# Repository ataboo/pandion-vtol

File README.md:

# Pandion VTOL

## Notes to Future

### Making Aft Prop Bi-directional

1. Connect to flight controller, test connection with BF-Configurator, but disconnect after.
2. Connect BL-Heli Configurator F-H-40 16.7, flash new or just configur as bi-directional.

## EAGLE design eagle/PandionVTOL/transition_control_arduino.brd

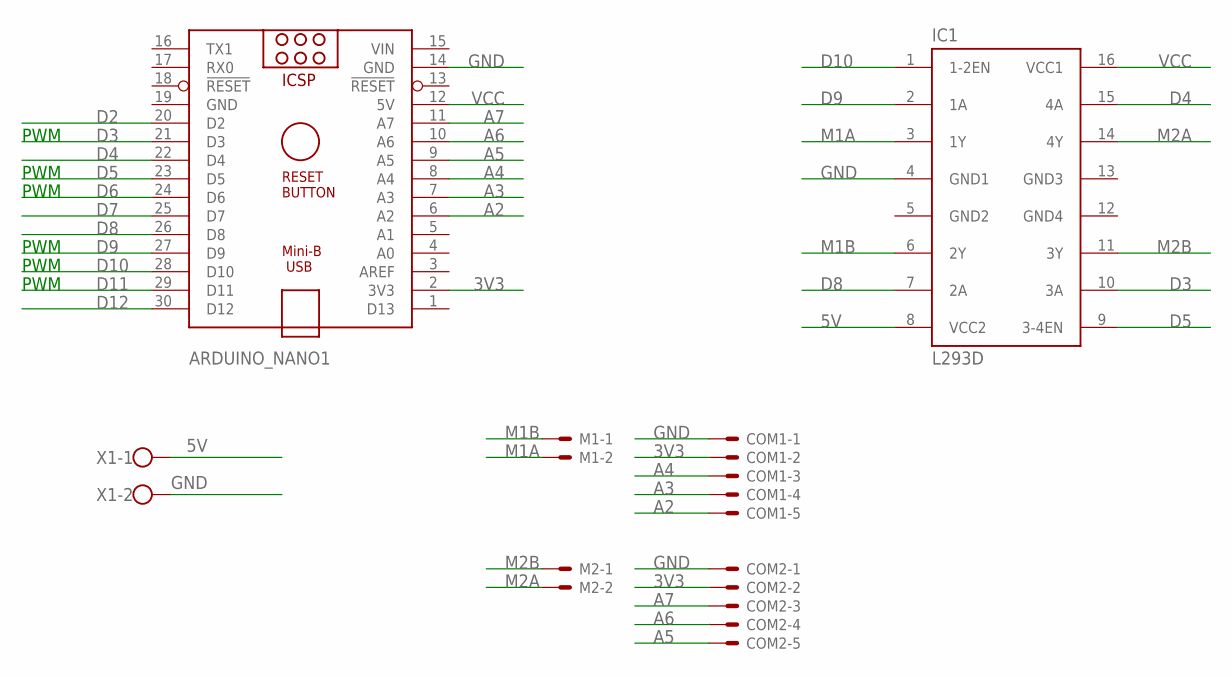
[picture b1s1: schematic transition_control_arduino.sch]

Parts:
ARDUINO_NANO1: ARDUINO_NANO
COM1, COM2: JST-XH-05-PIN-ROUND-PAD; JST-XH-05-PACKAGE-ROUND-PAD
IC1: L293D; DIL16
M1, M2: JST-XH-02-PIN-ROUND-PAD; JST-XH-02-PACKAGE-ROUND-PAD
X1: W237-102

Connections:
3V3: ARDUINO_NANO1.2 (3V3), COM1.2, COM2.2
5V: IC1.8 (VCC2), X1.1
A2: ARDUINO_NANO1.6 (A2), COM1.5
A3: ARDUINO_NANO1.7 (A3), COM1.4
A4: ARDUINO_NANO1.8 (A4), COM1.3
A5: ARDUINO_NANO1.9 (A5), COM2.5
A6: ARDUINO_NANO1.10 (A6), COM2.4
A7: ARDUINO_NANO1.11 (A7), COM2.3
D2: ARDUINO_NANO1.20 (D2)
D3: ARDUINO_NANO1.21 (D3), IC1.10 (3A)
D4: ARDUINO_NANO1.22 (D4), IC1.15 (4A)
D5: ARDUINO_NANO1.23 (D5), IC1.9 (3-4EN)
D6: ARDUINO_NANO1.24 (D6)
D7: ARDUINO_NANO1.25 (D7)
D8: ARDUINO_NANO1.26 (D8), IC1.7 (2A)
D9: ARDUINO_NANO1.27 (D9), IC1.2 (1A)
D10: ARDUINO_NANO1.28 (D10), IC1.1 (1-2EN)
D11: ARDUINO_NANO1.29 (D11)
D12: ARDUINO_NANO1.30 (D12)
GND: ARDUINO_NANO1.14 (GND), ARDUINO_NANO1.19 (GND), COM1.1, COM2.1, IC1.4 (GND1), X1.2
GND2: IC1.5 (GND2)
GND3: IC1.13 (GND3)
GND4: IC1.12 (GND4)
M1A: IC1.3 (1Y), M1.2
M1B: IC1.6 (2Y), M1.1
M2A: IC1.14 (4Y), M2.2
M2B: IC1.11 (3Y), M2.1
VCC: ARDUINO_NANO1.12 (5V), IC1.16 (VCC1)
VIN: ARDUINO_NANO1.15 (VIN)

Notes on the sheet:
PWM

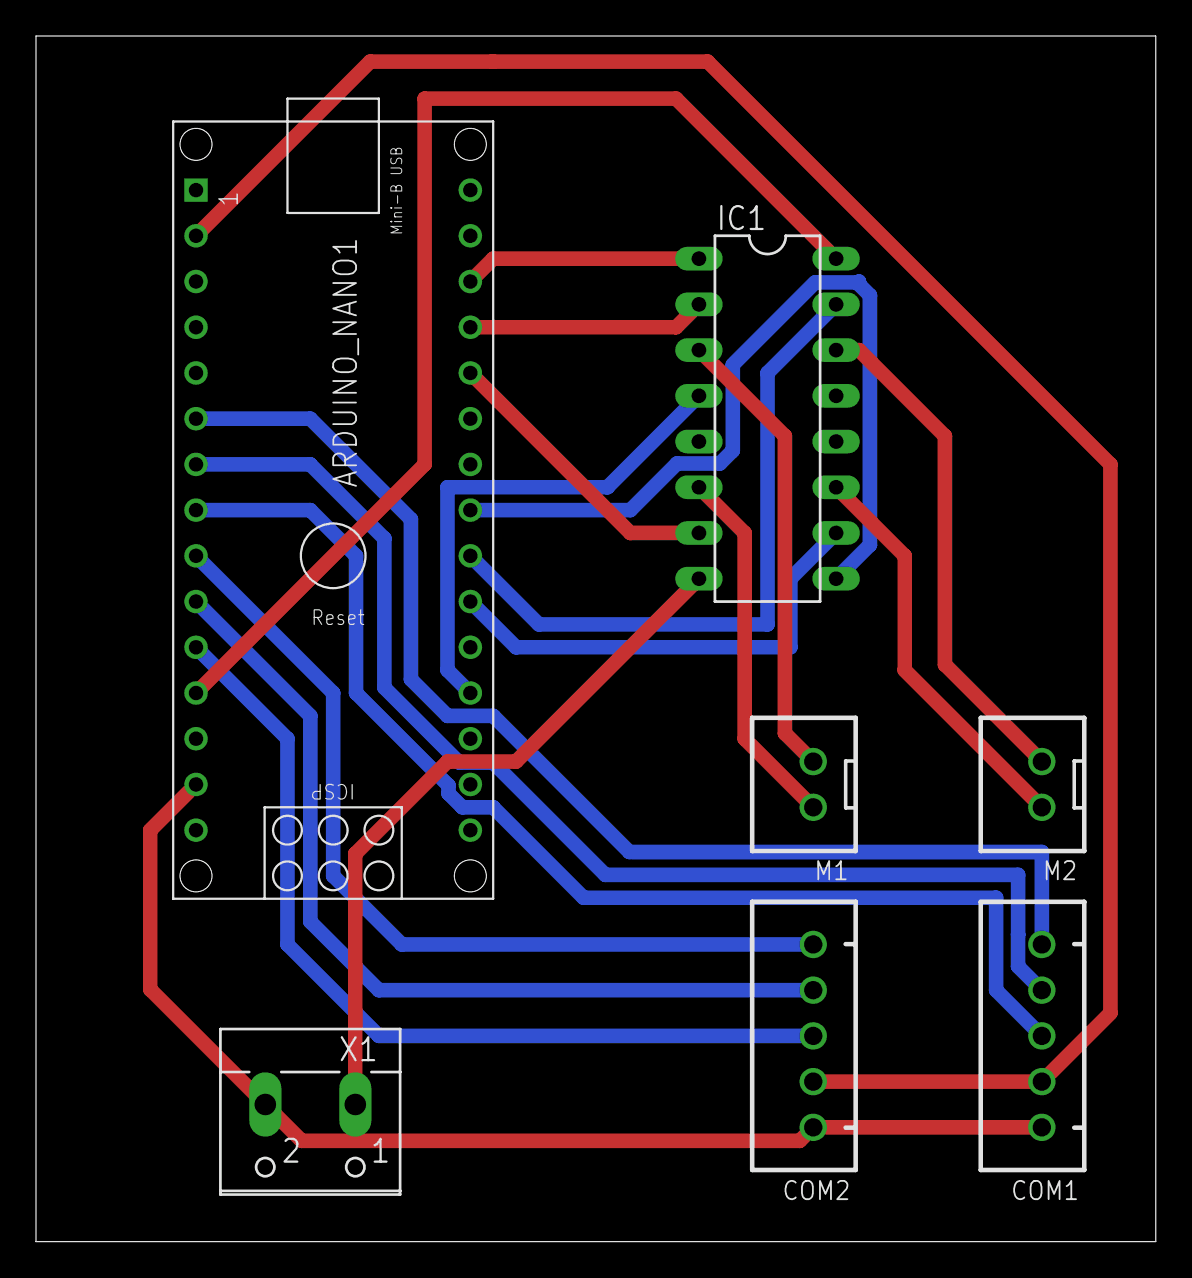
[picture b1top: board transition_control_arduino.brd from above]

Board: 2 copper layers, 62.2 x 67.0 mm, 7 parts (0 on the bottom side), 20 nets.

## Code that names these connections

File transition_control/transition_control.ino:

#include "AtaLogger.h"

#define M1A_PIN 3
#define M1B_PIN 4
#define M1P_PIN 5

#define M2A_PIN 6
#define M2B_PIN 7
#define M2P_PIN 8

#define TAG "TC"
#define TAG2 "TC2"

char write_buffer[32];
AtaLogger logger;

void setup() {
  AtaLoggerConfig logConfig;
  logConfig.baud_rate = 19200;
  logConfig.tags = (const char*){"tag1","tag2","TC"};
  logConfig.tag_count = 1;
  logger.Init(logConfig);
  
  pinMode(M1A_PIN, OUTPUT);
  pinMode(M1B_PIN, OUTPUT);
  pinMode(LED_BUILTIN, OUTPUT);
}

void loop() {
  digitalWrite(LED_BUILTIN, HIGH);
//  digitalWrite(M1A_PIN, HIGH);
//  digitalWrite(M1B_PIN, LOW);
  for(int i=0; i<11; i++) {
    logger.Info(TAG, "Duty: %d", i * 10);
    logger.Info(TAG2, "other tag!");
    
    int duty = i * 255 /10;
    analogWrite(M1P_PIN, duty);
    delay(1000);
  }

//  analogWrite(M1P_PIN, 0);
  digitalWrite(LED_BUILTIN, LOW);
  delay(1000);
}

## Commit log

2020-02-08 Added eagle cad transition arduino
2020-02-12 Adding esp-transition from basic PWM example
2020-02-12 Working on transition
2020-02-12 adding atalogger and pandionTC libraries
2020-02-12 Made AtaLogger testible, using cmake
2020-02-12 removed sdkconfig
2020-02-12 removed .vscode
2020-02-13 expanding to motor control compoennt
2020-02-15 added encoder counter
2020-02-17 adding bus mixer
2020-02-17 Adding pandion bus mixer and uart config
2020-02-18 working on bus mixer
2020-02-19 adding servo control
2020-02-24 working on servo control
2020-03-02 more servo control fixes
2020-03-09 receiver working with PWM output
2020-03-13 Adding MPU6050 gyro
2020-03-14 added console plotter, adding pid
2020-03-15 working on flight control
2020-03-16 first functional test
2020-03-22 adding dshot esc control
2020-03-22 added dshot esc
2020-03-23 tweaks, bench test success
2020-03-26 Done pandion esp32 board schematic
2020-03-28 esp32 board update
2020-03-28 renamed to esp-pandion
2020-03-29 added axis curve
2020-03-30 Getting bi-directional dshot going
2020-04-07 tweaked flight control pitch
2020-04-07 pids tuned for 0.2.3 flight
2020-04-10 added battery meter
2020-04-11 Added battery voltage monitoring
2020-04-12 started ibus-sensors
2020-04-20 refactoring ibus for sensors
2020-04-21 working on ibus sensors
2020-04-21 working on ibus sensor
2020-04-21 ibus sensor functional
2020-04-23 more ibus work
2020-04-23 updating ibus
2020-04-24 ibus working with battery meter
2020-04-25 more flight control refactor, using timer loop
2020-04-26 pid tuning
2020-04-26 Adding wifi ap
2020-05-02 Adding tcp server
2020-05-03 fixed elevator
2020-05-04 increased aft prop factor
2020-05-04 added python tcp client
2020-06-12 started on wifi tuning
2020-06-12 started on positive stability
2020-06-13 added cmake config to vscode workspace
2020-06-13 refactoring positive stability, adding vscode settings
2020-06-14 checkpoint before moving flight control components as sub-components
2020-06-14 Added positive stability, refactored flight control common
2020-06-27 Using neutral stab for horizontal
2020-06-29 fixed flight control
2020-07-06 Added icon, using verb, noun in command
2020-07-07 Better command handling, adding lookup for servo end-points
2020-07-10 moved nvs to more generic config_db
2020-07-15 working on wifi tuning
2020-07-15 getting remote settings working
2020-07-31 re-enabling pitch, more bugs
2022-06-22 Bump numpy from 1.18.1 to 1.22.0 in /utils/console-plotter
    Bumps [numpy](https://github.com/numpy/numpy) from 1.18.1 to 1.22.0.
    - [Release notes](https://github.com/numpy/numpy/releases)
    - [Changelog](https://github.com/numpy/numpy/blob/main/doc/HOWTO_RELEASE.rst)
    - [Commits](https://github.com/numpy/numpy/compare/v1.18.1...v1.22.0)
    ---
    updated-dependencies:
